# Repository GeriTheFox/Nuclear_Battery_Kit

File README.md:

# Nuclear_Battery_Kit
Bring Your Own Tritium Radioisotope Photovoltaic Cell Kit

https://www.sparkfun.com/products/14773

After we caught sight of some very cool folks online making their very own homemade nuclear batteries, we knew we had to give it a go!

The device in question is actually known as a “Radioisotope Photovoltaic Generator” or “Photobetavoltaic Generator,” and it’s a pretty clever design: Glowing glass pills filled with Tritium gas and coated in a phosphorescent material are sandwiched between two photovoltaic cells. The beta radiation emitted by the Tritium is blocked by the glass walls of the pill, but they cause the phosphorescent coating to glow. This light has no trouble passing through the glass and lands on the photovoltaic cells where it produces a small amount of electricity! Commercial Tritium batteries — like those produced by City Labs — cut out the middleman by using betavoltaic (as opposed to photovoltaic) cells in direct contact with Tritium gas. Those commercial devices are more rugged and efficient, but come with a very large price tag (thousands of USD per unit). On the other hand, homemade devices constructed using the packing tape sandwich method are as cheap as it gets, but aren’t particularly rugged.

This kit provides a good compromise between price and quality of construction. We’ve designed carrier boards for both of the photovoltaic cells which we supply pre-soldered and fixed to the boards with chipbonder. We’ve also designed and cast custom silicone rubber grommets which cushion the Tritium vials between the two photovoltaic cells, preventing the cells from getting scratched or chipped and — most importantly — the vials from getting broken. The carrier boards also allow you to choose whether the photovoltaic cells are wired in series or parallel and provide you with breadboard compatible pin spacing for the battery terminals.

So how much power does it make? Not much. The best measurement we were able to make suggests that the maximum power point of this arrangement is 25nW, if you can build a circuit that loads it properly (between 20 and 30nA at about 0.6v). Further experiments show that the battery will — given enough time — charge a capacitor to a voltage of 1.5 volts. Using this battery to do any work will likely involve a clever energy harvesting circuit, but keep in mind that this tiny amount of power will continue to flow for about 20 years — the half life of Tritium being 12 years. It’s also worth noting that these measurements were taken using green colored tritium tubes from aliexpress, your mileage may vary with the color and quality of your Tritium glow tubes. Feel free to experiment!

Because the silicone gasket supplied with this kit is not perfectly opaque, you will need to take any measurements in a light-proof enclosure (we made a little box out of copper foil tape) otherwise you will be getting inflated readings from ambient light striking the photovoltaics. You may also fill in the gaps around your gasket using an opaque epoxy resin. In practice, though, it may be beneficial to grab whatever “bonus energy” you can and only rely on the tritium vials when there’s nothing else.

This Kit is B.Y.O.T (Bring Your Own Tritium)
Due to fairly predictable shipping and handling restrictions, we are — unfortunately — unable to provide you with the tritium glow vials that you will need to build a functioning battery. We can, however, send you in the right direction to acquire the vials on their own. This kit requires 10 pcs of 2x12mm Tritium Glow Vials, which — as of the time this product was released — should set you back between 90 and 150 USD. You can find them at the link above and also via sites such as banggood.com under the name “Tritium Vial” or “Betalight”.

Experimental Product: SparkX products are rapidly produced to bring you the most cutting edge technology as it becomes available. These products are tested but come with no guarantees. Live technical support is not available for SparkX products. Head on over to our forum for support or to ask a question.

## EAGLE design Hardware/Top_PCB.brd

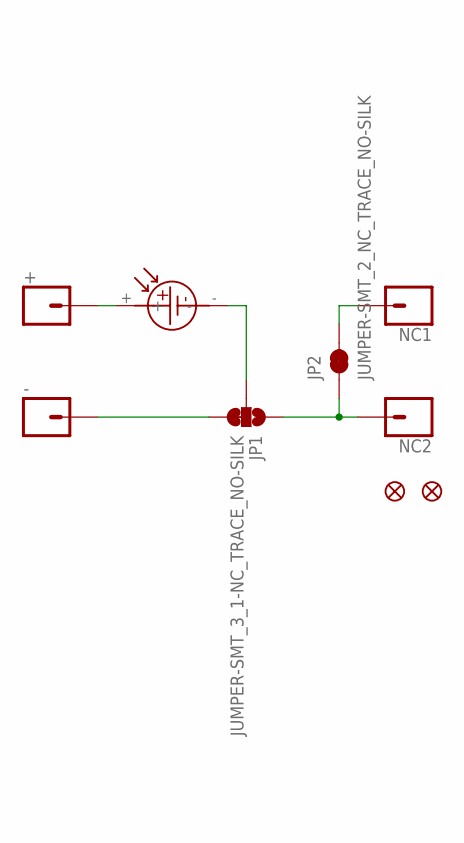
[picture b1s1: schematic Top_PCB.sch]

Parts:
+: CONN_01; 1X01
-: CONN_01; 1X01
FD1, FD2: FIDUCIALUFIDUCIAL; FIDUCIAL-MICRO
JP1: JUMPER-SMT_3_1-NC_TRACE_NO-SILK; SMT-JUMPER_3_1-NC_TRACE_NO-SILK
JP2: JUMPER-SMT_2_NC_TRACE_NO-SILK; SMT-JUMPER_2_NC_TRACE_NO-SILK
NC1, NC2: CONN_01; 1X01
U$1: 9X20_AMORPHOUS_PV; 20X9MM

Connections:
unnamed: +.1, U$1.+
unnamed: JP1.2, U$1.-
unnamed: -.1, JP1.3
unnamed: JP1.1, JP2.1, NC2.1
unnamed: JP2.2, NC1.1

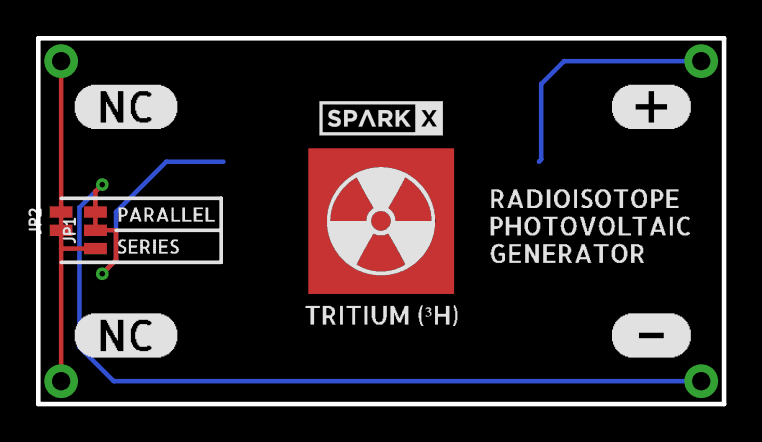
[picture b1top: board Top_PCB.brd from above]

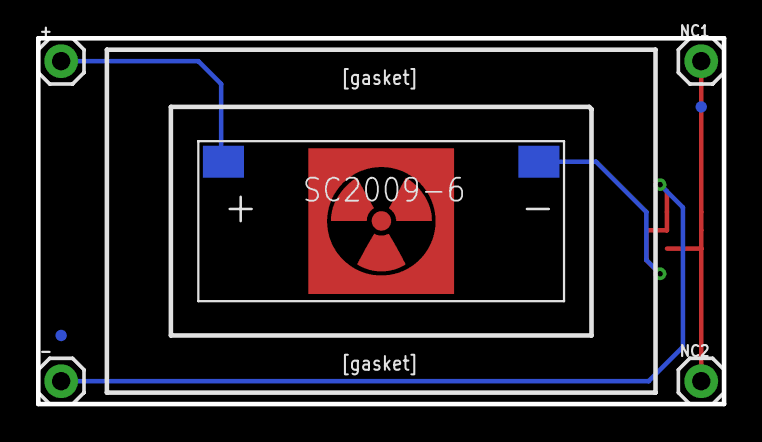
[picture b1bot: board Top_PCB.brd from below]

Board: 2 copper layers, 38.1 x 20.3 mm, 21 parts (7 on the bottom side), 5 nets.

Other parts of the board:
U$2: RADIATION_TREFOIL_SIGN_SYMBOL_WARNING_SIGN_SYMBOL_CLASSIC_R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
U$3: TRITIUM_##H#0
U$4: SPARKX-SMALL
U$5: RADIOISOTOPE0
U$6: PHOTOVOLTAIC1
U$7: PARALLEL1
U$8: SERIES0
U$9: #0
U$10: #1
U$11, U$12: NC0
U$13: GENERATOR0

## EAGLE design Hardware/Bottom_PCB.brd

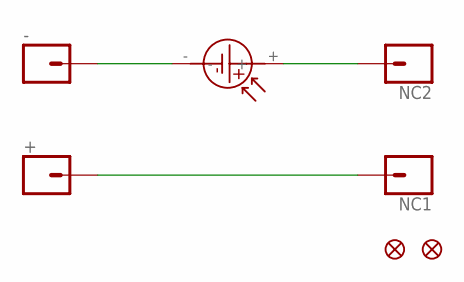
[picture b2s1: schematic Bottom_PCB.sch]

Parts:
+: CONN_01; 1X01
-: CONN_01; 1X01
FD1, FD2: FIDUCIALUFIDUCIAL; FIDUCIAL-MICRO
NC1, NC2: CONN_01; 1X01
U$1: 9X20_AMORPHOUS_PV; 20X9MM

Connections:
unnamed: +.1, NC1.1
unnamed: -.1, U$1.-
unnamed: NC2.1, U$1.+

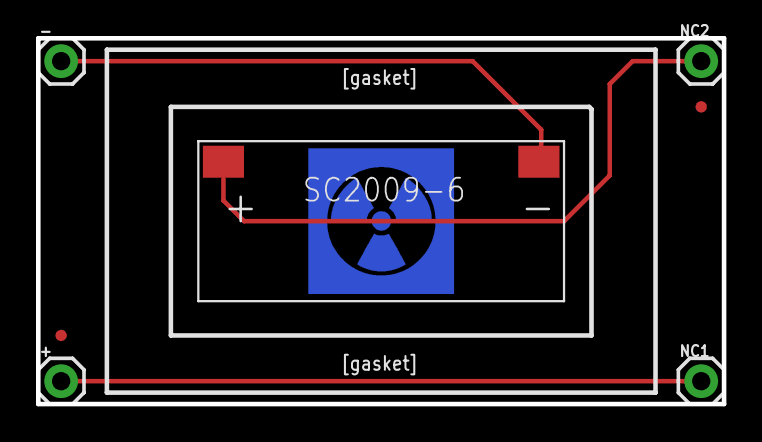
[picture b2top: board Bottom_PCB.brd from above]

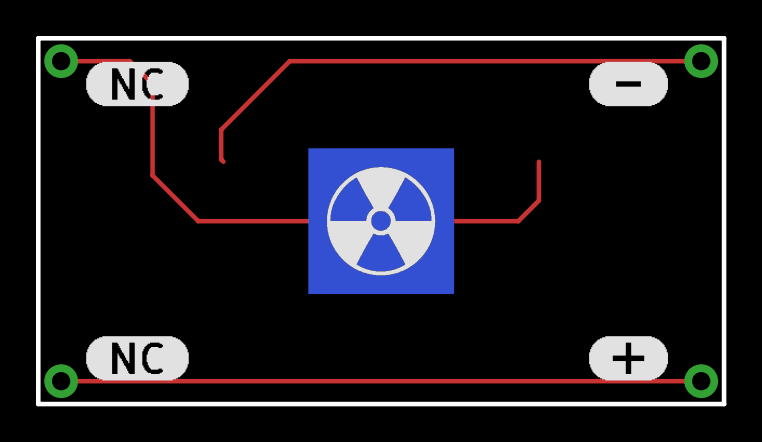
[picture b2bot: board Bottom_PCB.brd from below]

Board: 2 copper layers, 38.1 x 20.3 mm, 12 parts (5 on the bottom side), 3 nets.

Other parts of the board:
U$2: #0
U$3: #1
U$4, U$6: NC0
U$5: RADIATION_TREFOIL_SIGN_SYMBOL_WARNING_SIGN_SYMBOL_CLASSIC_R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

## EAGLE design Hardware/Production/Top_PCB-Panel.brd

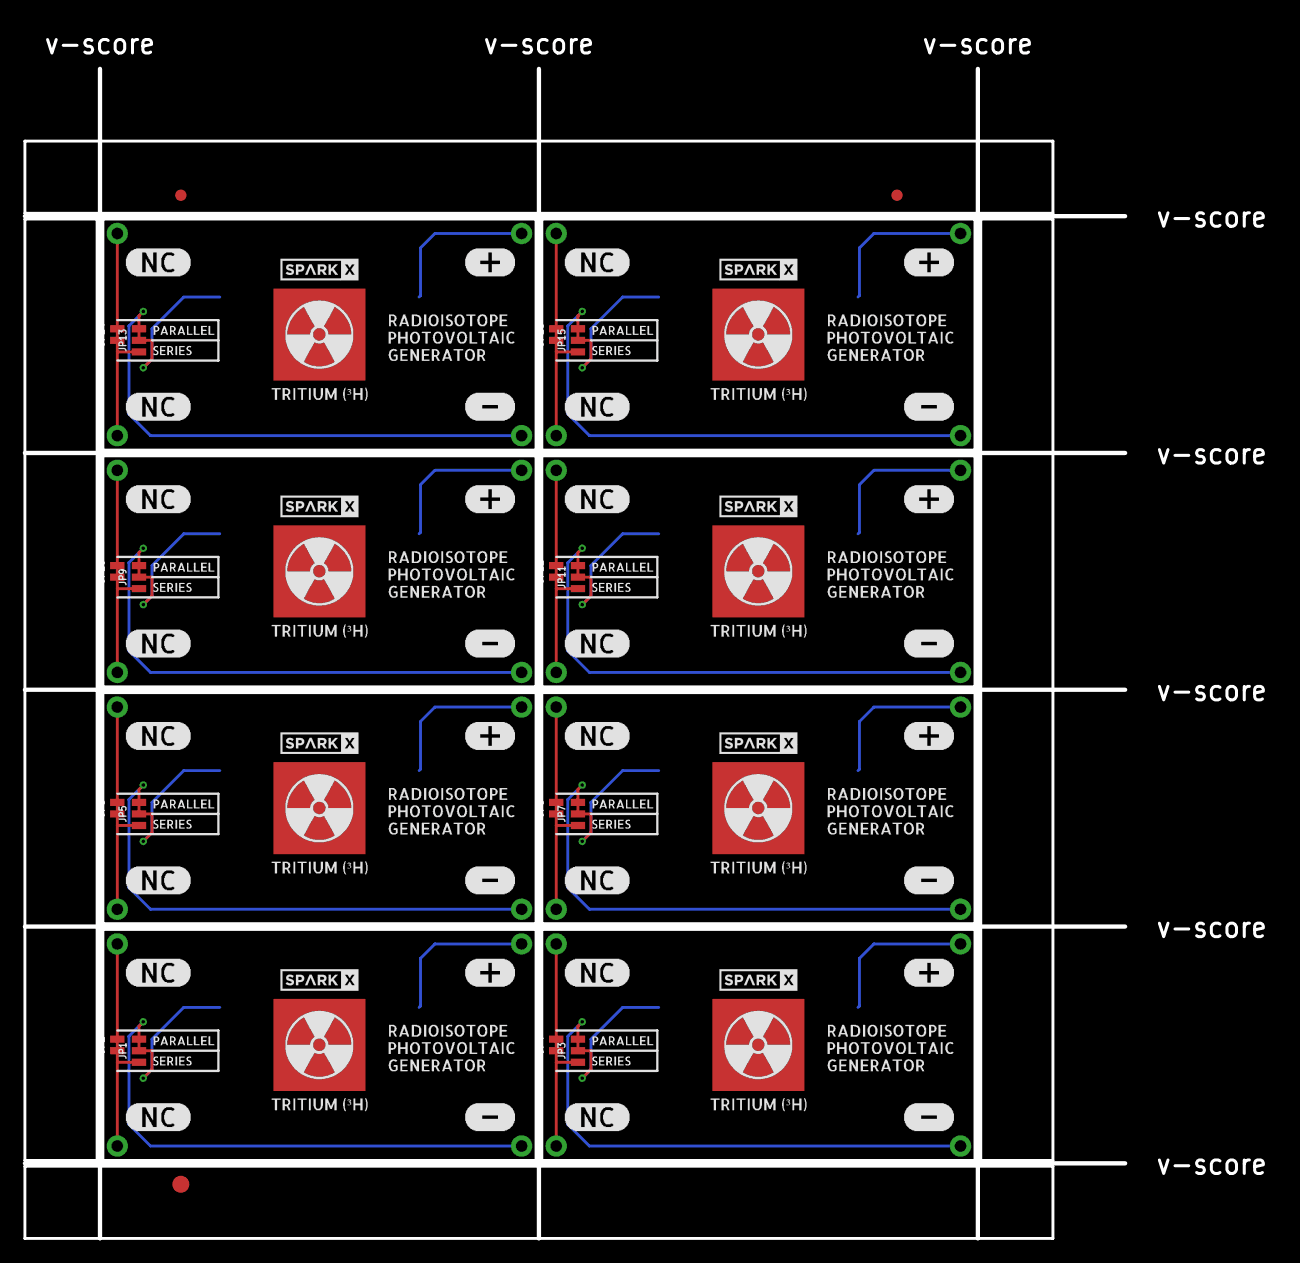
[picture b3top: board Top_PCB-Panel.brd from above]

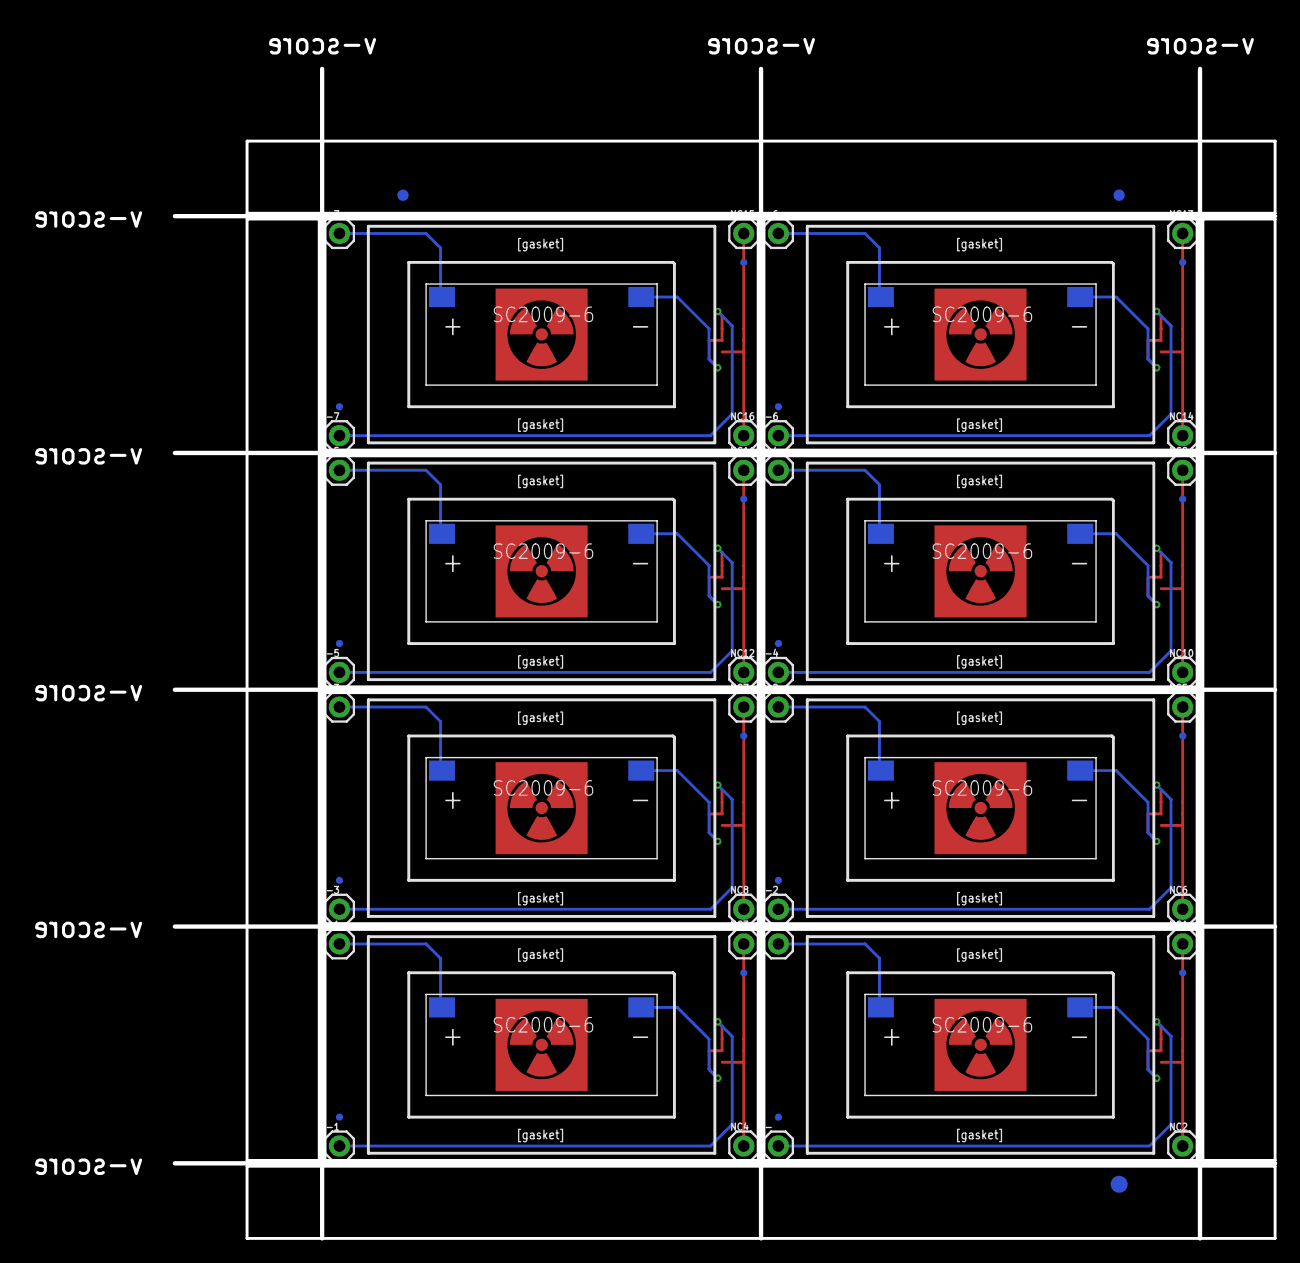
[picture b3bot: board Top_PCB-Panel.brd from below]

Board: 2 copper layers, 96.8 x 102.9 mm, 174 parts (59 on the bottom side), 40 nets.

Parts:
+, +1, +2, +3, +4, +5, +6, +7: 1X01
-, -1, -2, -3, -4, -5, -6, -7: 1X01
E$1, E$2, E$3, E$4: FIDUCIAL-1X2
E$5, E$6: FIDUCIAL-1.5X3
FD1, FD2, FD3, FD4, FD5, FD6, FD7, FD8, FD9, FD10, FD11, FD12, FD13, FD14, FD15, FD16: FIDUCIALUFIDUCIAL; FIDUCIAL-MICRO
JP1, JP3, JP5, JP7, JP9, JP11, JP13, JP15: JUMPER-SMT_3_1-NC_TRACE_NO-SILK; SMT-JUMPER_3_1-NC_TRACE_NO-SILK
JP2, JP4, JP6, JP8, JP10, JP12, JP14, JP16: JUMPER-SMT_2_NC_TRACE_NO-SILK; SMT-JUMPER_2_NC_TRACE_NO-SILK
NC1, NC2, NC3, NC4, NC5, NC6, NC7, NC8, NC9, NC10, NC11, NC12, NC13, NC14, NC15, NC16: 1X01
U$1, U$14, U$27, U$40, U$53, U$66, U$79, U$92: 9X20_AMORPHOUS_PV; 20X9MM
U$2, U$15, U$28, U$41, U$54, U$67, U$80, U$93: RADIATION_TREFOIL_SIGN_SYMBOL_WARNING_SIGN_SYMBOL_CLASSIC_R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
U$3, U$16, U$29, U$42, U$55, U$68, U$81, U$94: TRITIUM_##H#0
U$4, U$17, U$30, U$43, U$56, U$69, U$82, U$95: SPARKX-SMALL
U$5, U$24, U$37, U$50, U$63, U$76, U$89, U$102: RADIOISOTOPE0
U$6, U$25, U$38, U$51, U$64, U$77, U$90, U$103: PHOTOVOLTAIC1
U$7, U$18, U$31, U$44, U$57, U$70, U$83, U$96: PARALLEL1
U$8, U$19, U$32, U$45, U$58, U$71, U$84, U$97: SERIES0
U$9, U$20, U$33, U$46, U$59, U$72, U$85, U$98: #0
U$10, U$21, U$34, U$47, U$60, U$73, U$86, U$99: #1
U$11, U$12, U$22, U$23, U$35, U$36, U$48, U$49, U$61, U$62, U$74, U$75, U$87, U$88, U$100, U$101: NC0
U$13, U$26, U$39, U$52, U$65, U$78, U$91, U$104: GENERATOR0

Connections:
unnamed: +.1, U$1.+
unnamed: JP1.2, U$1.-
unnamed: -.1, JP1.3
unnamed: JP1.1, JP2.1, NC2.1
unnamed: JP2.2, NC1.1
unnamed: +1.1, U$14.+
unnamed: -1.1, JP3.3
unnamed: JP3.1, JP4.1, NC4.1
unnamed: JP4.2, NC3.1
unnamed: JP3.2, U$14.-
unnamed: +2.1, U$27.+
unnamed: -2.1, JP5.3
unnamed: JP5.1, JP6.1, NC6.1
unnamed: JP6.2, NC5.1
unnamed: JP5.2, U$27.-
unnamed: +3.1, U$40.+
unnamed: -3.1, JP7.3
unnamed: JP7.1, JP8.1, NC8.1
unnamed: JP8.2, NC7.1
unnamed: JP7.2, U$40.-
unnamed: +4.1, U$53.+
unnamed: -4.1, JP9.3
unnamed: JP9.1, JP10.1, NC10.1
unnamed: JP10.2, NC9.1
unnamed: JP9.2, U$53.-
unnamed: +5.1, U$66.+
unnamed: -5.1, JP11.3
unnamed: JP11.1, JP12.1, NC12.1
unnamed: JP12.2, NC11.1
unnamed: JP11.2, U$66.-
unnamed: +6.1, U$79.+
unnamed: -6.1, JP13.3
unnamed: JP13.1, JP14.1, NC14.1
unnamed: JP14.2, NC13.1
unnamed: JP13.2, U$79.-
unnamed: +7.1, U$92.+
unnamed: -7.1, JP15.3
unnamed: JP15.1, JP16.1, NC16.1
unnamed: JP16.2, NC15.1
unnamed: JP15.2, U$92.-

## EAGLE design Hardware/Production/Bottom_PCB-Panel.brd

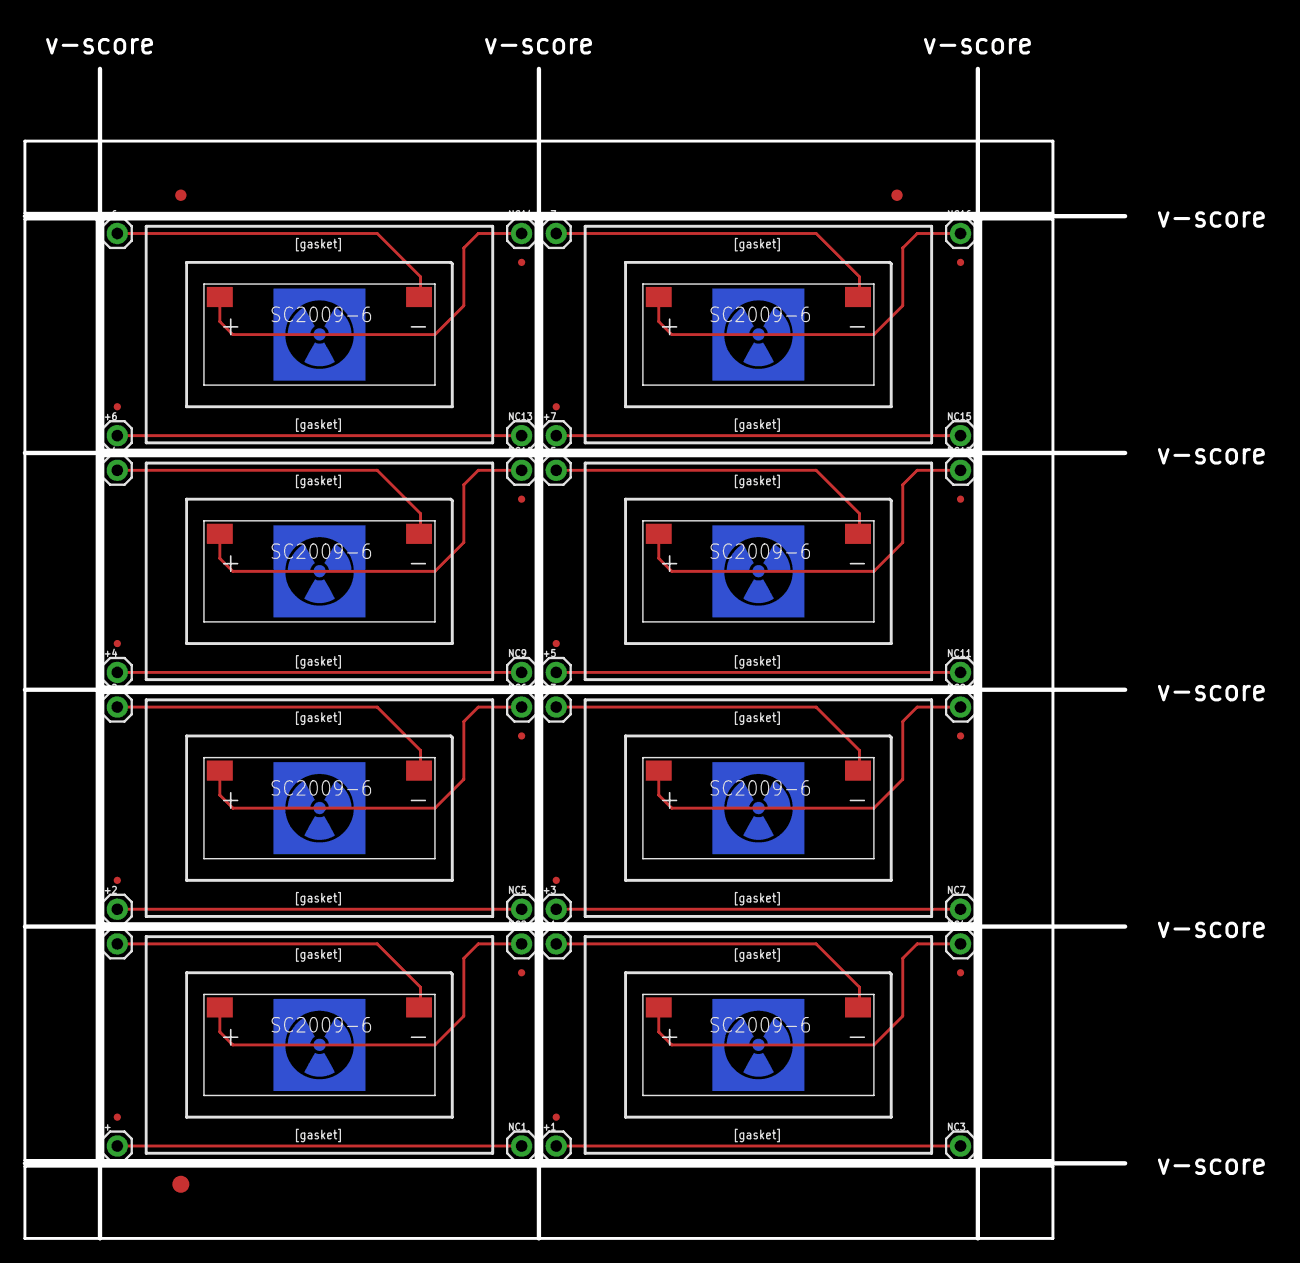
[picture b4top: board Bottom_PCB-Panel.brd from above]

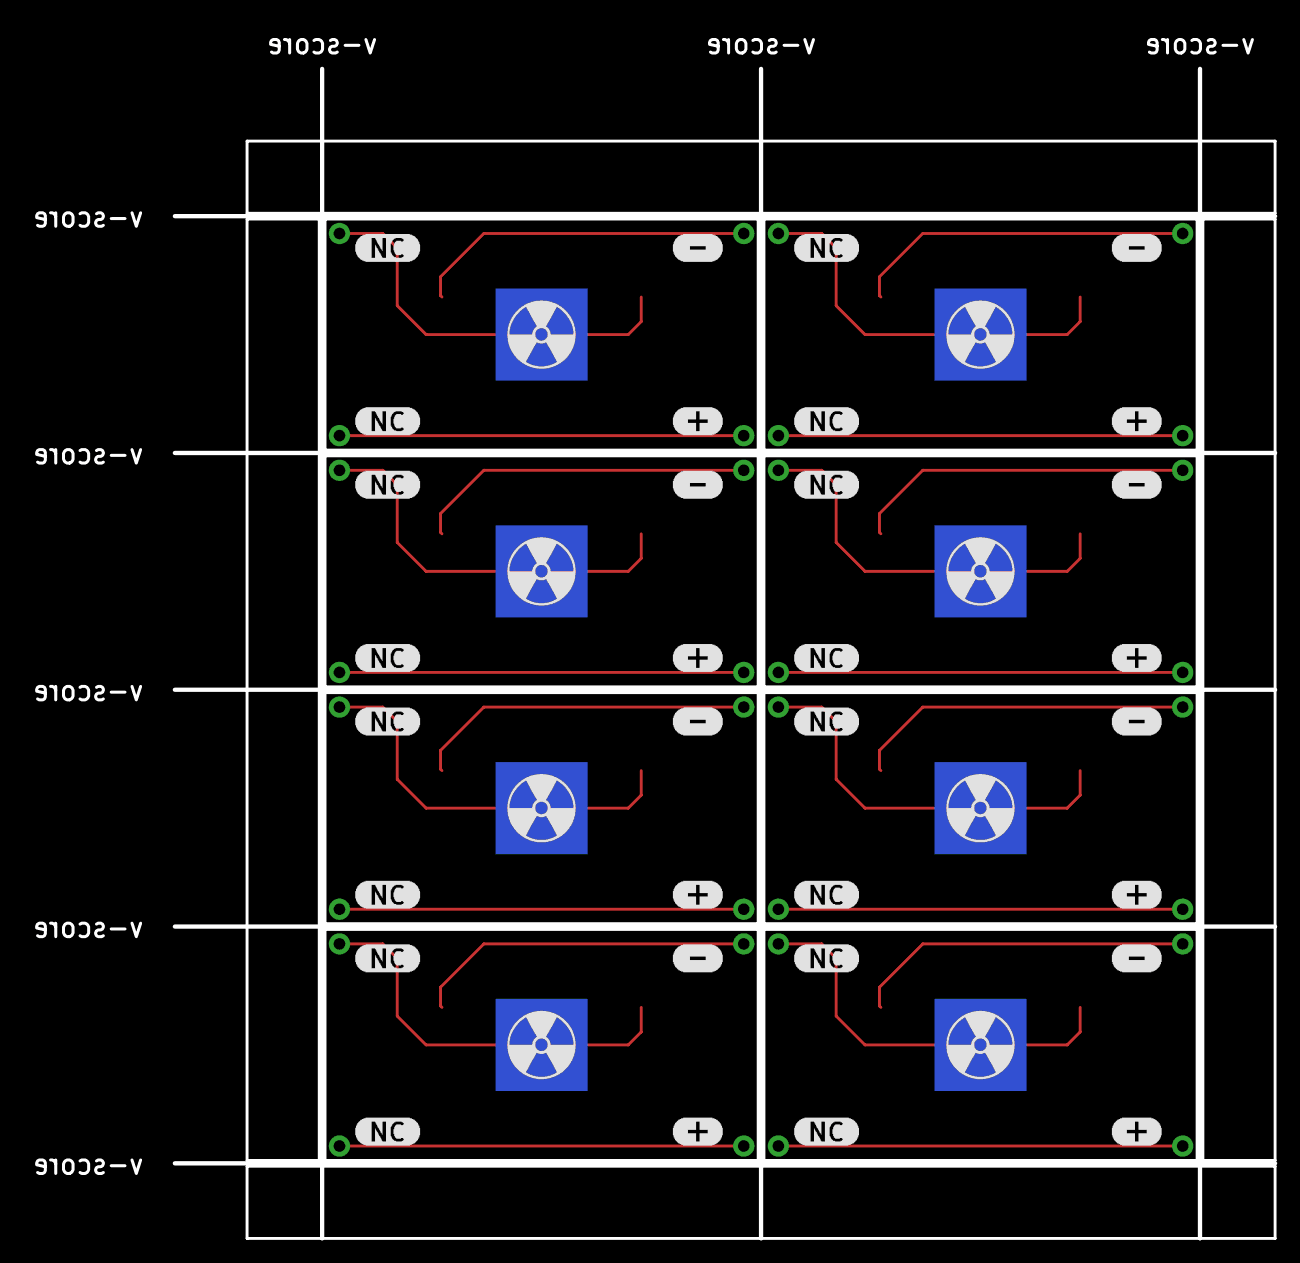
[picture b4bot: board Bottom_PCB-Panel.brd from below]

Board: 2 copper layers, 96.8 x 102.9 mm, 99 parts (40 on the bottom side), 24 nets.

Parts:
+, +1, +2, +3, +4, +5, +6, +7: 1X01
-, -1, -2, -3, -4, -5, -6, -7: 1X01
E$1, E$2: FIDUCIAL-1X2
E$3: FIDUCIAL-1.5X3
FD1, FD2, FD3, FD4, FD5, FD6, FD7, FD8, FD9, FD10, FD11, FD12, FD13, FD14, FD15, FD16: FIDUCIALUFIDUCIAL; FIDUCIAL-MICRO
NC1, NC2, NC3, NC4, NC5, NC6, NC7, NC8, NC9, NC10, NC11, NC12, NC13, NC14, NC15, NC16: 1X01
U$1, U$7, U$13, U$19, U$25, U$31, U$37, U$43: 9X20_AMORPHOUS_PV; 20X9MM
U$2, U$8, U$14, U$20, U$26, U$32, U$38, U$44: #0
U$3, U$9, U$15, U$21, U$27, U$33, U$39, U$45: #1
U$4, U$6, U$10, U$12, U$16, U$18, U$22, U$24, U$28, U$30, U$34, U$36, U$40, U$42, U$46, U$48: NC0
U$5, U$11, U$17, U$23, U$29, U$35, U$41, U$47: RADIATION_TREFOIL_SIGN_SYMBOL_WARNING_SIGN_SYMBOL_CLASSIC_R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

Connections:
unnamed: +.1, NC1.1
unnamed: -.1, U$1.-
unnamed: NC2.1, U$1.+
unnamed: +1.1, NC3.1
unnamed: -1.1, U$7.-
unnamed: NC4.1, U$7.+
unnamed: +2.1, NC5.1
unnamed: -2.1, U$13.-
unnamed: NC6.1, U$13.+
unnamed: +3.1, NC7.1
unnamed: -3.1, U$19.-
unnamed: NC8.1, U$19.+
unnamed: +4.1, NC9.1
unnamed: -4.1, U$25.-
unnamed: NC10.1, U$25.+
unnamed: +5.1, NC11.1
unnamed: -5.1, U$31.-
unnamed: NC12.1, U$31.+
unnamed: +6.1, NC13.1
unnamed: -6.1, U$37.-
unnamed: NC14.1, U$37.+
unnamed: +7.1, NC15.1
unnamed: -7.1, U$43.-
unnamed: NC16.1, U$43.+

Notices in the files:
parts and their libraries:
SparkFun-Connectors: Licensing: Creative Commons ShareAlike 4.0 International - https://creativecommons.org/licenses/by-sa/4.0
